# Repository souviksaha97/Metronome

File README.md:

# Metronome
ATTiny85 based metronome

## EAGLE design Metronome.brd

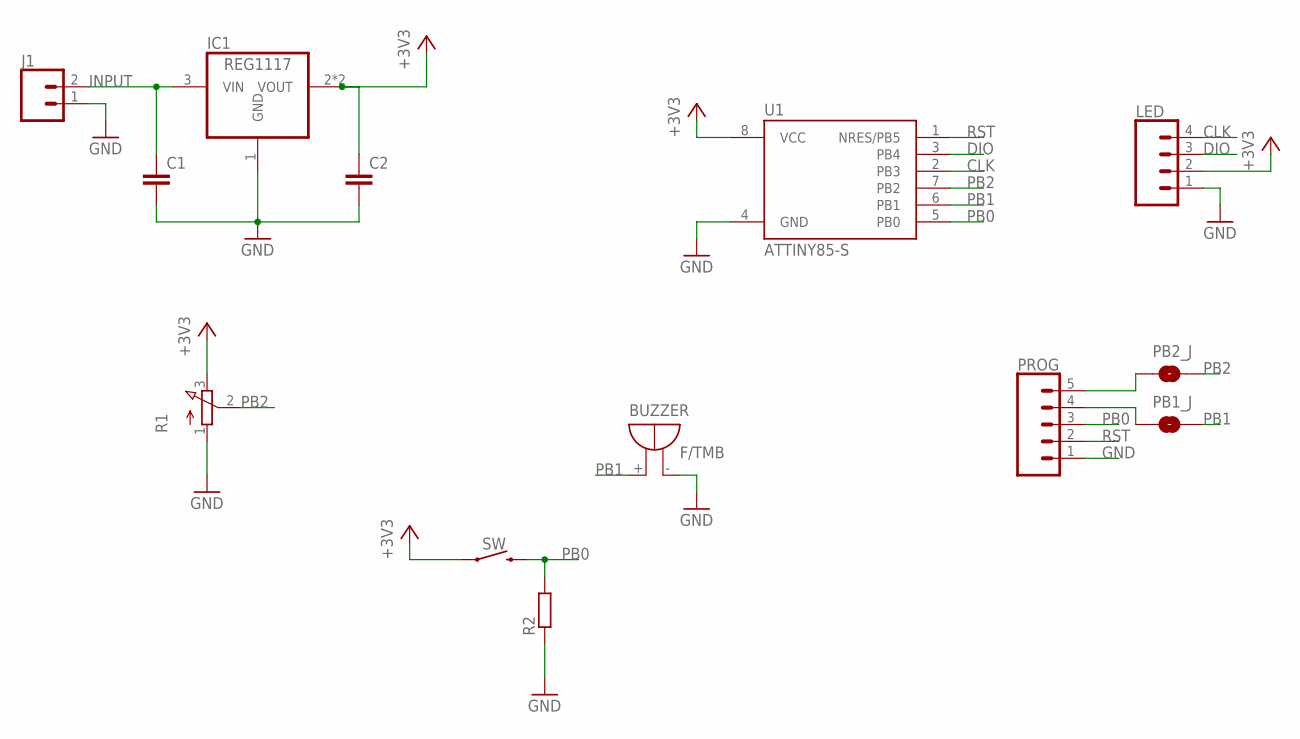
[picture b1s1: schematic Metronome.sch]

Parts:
BUZZER: F/TMB
C1, C2: C-EUC1206; C1206
IC1: REG1117; SOT223
J1: CONN_02POLAR; MOLEX-1X2
LED: CONN_04; 1X04
PB1_J, PB2_J: JUMPER-SMT_2_NO_NO-SILK; SMT-JUMPER_2_NO_NO-SILK
PROG: CONN_05; 1X05
R1: 3RP/1610N
R2: R-EU_R1206; R1206
SW: MOMENTARY-SWITCH-SPST-PTH-12MM; TACTILE_SWITCH_PTH_12MM
U1: ATTINY85-S; SOIC8_EIAJ_208MIL

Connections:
+3V3: C2.1, IC1.2 (VOUT), IC1.4 (VOUT), LED.2, R1.3 (E), SW.1, U1.8 (VCC)
CLK: LED.4, U1.2 (PB3)
DIO: LED.3, U1.3 (PB4)
GND: BUZZER.-, C1.2, C2.2, IC1.1 (GND), J1.1, LED.1, PROG.1, R1.1 (A), R2.1, U1.4 (GND)
INPUT: C1.1, IC1.3 (VIN), J1.2
unnamed: PB2_J.1, PROG.5
unnamed: PB1_J.1, PROG.4
PB0: PROG.3, R2.2, SW.3 (2), U1.5 (PB0)
PB1: BUZZER.+, PB1_J.2, U1.6 (PB1)
PB2: PB2_J.2, R1.2 (S), U1.7 (PB2)
RST: PROG.2, U1.1 (NRES/PB5)

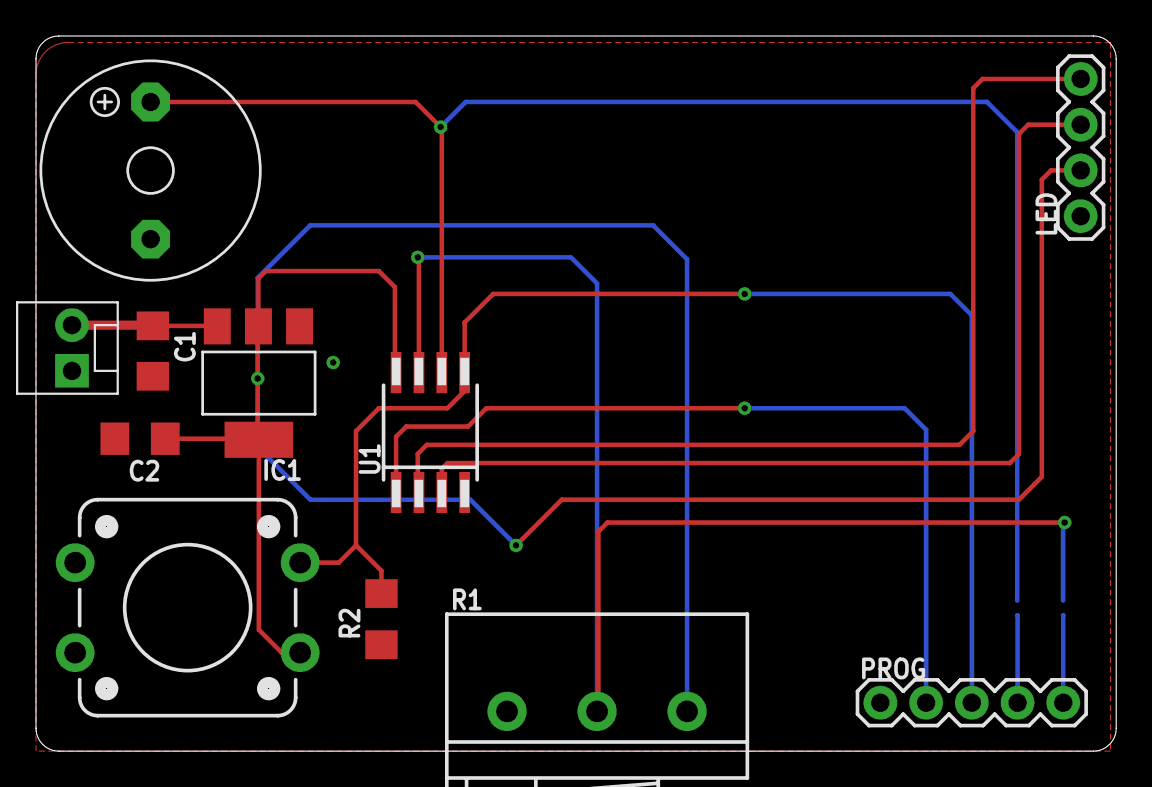
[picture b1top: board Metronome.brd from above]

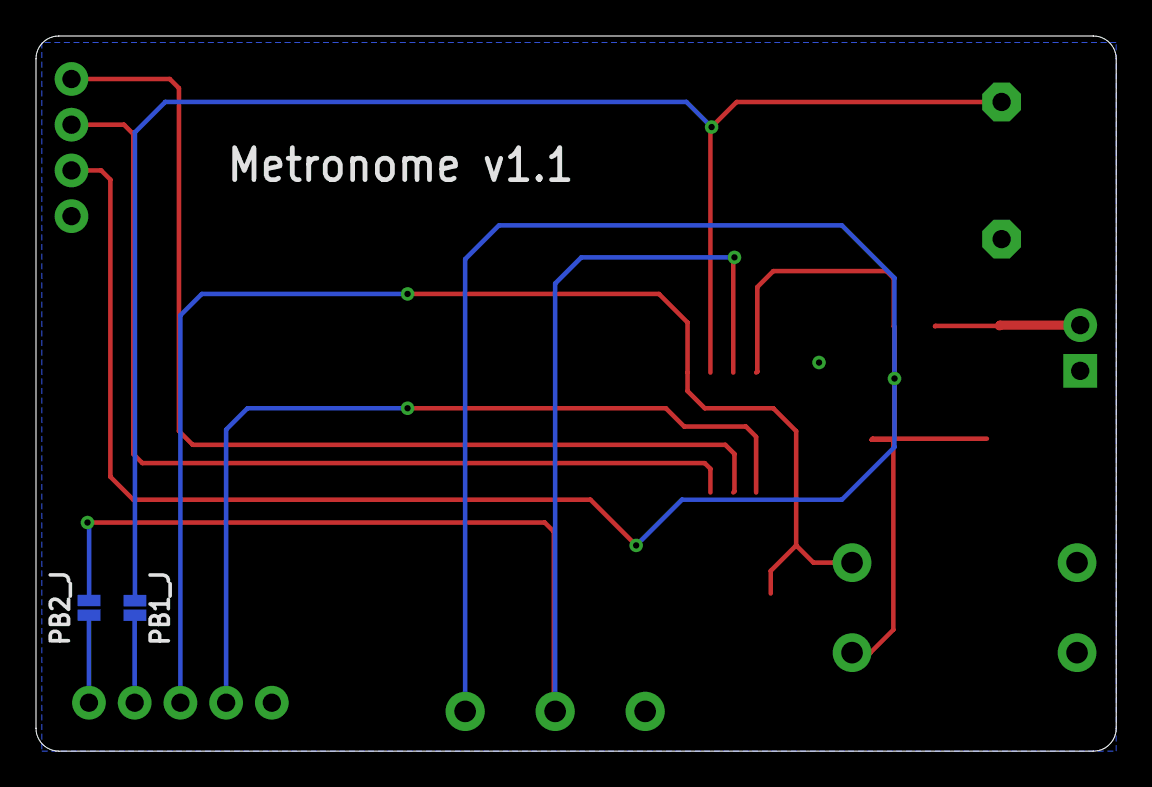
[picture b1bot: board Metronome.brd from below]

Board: 2 copper layers, 60.0 x 39.7 mm, 13 parts (2 on the bottom side), 11 nets.

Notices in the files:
parts and their libraries:
SparkFun-Connectors: Licensing: Creative Commons ShareAlike 4.0 International - https://creativecommons.org/licenses/by-sa/4.0
